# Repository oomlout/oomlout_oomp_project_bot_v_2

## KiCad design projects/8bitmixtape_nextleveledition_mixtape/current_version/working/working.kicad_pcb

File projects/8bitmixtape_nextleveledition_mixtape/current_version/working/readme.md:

# nextleveledition
 
## summary 
* id: 8bitmixtape_nextleveledition_mixtape
* user: 8bitmixtape
* name: nextleveledition
* board: mixtape
* repo: https://github.com/8BitMixtape/NextLevelEdition

* src_file_repo_sch: 
* src_file_repo_sch_link: https://github.com/8BitMixtape/NextLevelEdition/tree/master/
* full details link: https://github.com/oomlout/oomlout_oomp_project_bot_v_2/tree/main/projects/8bitmixtape_nextleveledition_mixtape/current_version/working  

## schematic  
  
[schematic (pdf)](working_schematic.pdf) 

## pcb  

[board (pdf)](working.pdf)  

## working_bom
| Id | Designator | Footprint | Quantity | Designation | Supplier and ref |  | None | 
| --- | --- | --- | --- | --- | --- | --- | --- | 
| 1 | R12,R11 | 0603-RES | 2 | 22 |  |  | [''] | 
| 2 | R6 | 0603-RES | 1 | 10K |  |  | [''] | 
| 3 | LED3 | LED-0603 | 1 | Green |  |  | [''] | 
| 4 | S1 | TASTER-9314_SMD | 1 | Left |  |  | [''] | 
| 5 | BAT+0,BAT-0 | SMD2,54-5,08 | 2 |  |  |  | [''] | 
| 6 | C12,C2,C6,C8,C11,C3 | 0603-CAP | 6 | 1uF |  |  | [''] | 
| 7 | SD0 | MICROSD | 1 | MICROSD |  |  | [''] | 
| 8 | U1 | SOT23-5 | 1 | MCP73831 |  |  | [''] | 
| 9 | U$4 | FUNNEL_LOGO_BOTTOM_V2 | 1 | FIO_LOGOV2 |  |  | [''] | 
| 10 | X1 | USB_B_SMD | 1 | USB_B_SMD |  |  | [''] | 
| 11 | C9 | 0603-CAP | 1 | 4.7uF |  |  | [''] | 
| 12 | C1,C13 | EIA3216 | 2 | 10uF |  |  | [''] | 
| 13 | R16,R13,R4,R10,R3,R7 | 0603-RES | 6 | 330 |  |  | [''] | 
| 14 | R2,R1 | 0603-RES | 2 | 33 |  |  | [''] | 
| 15 | PAD2,PAD3,PAD1 | SMD1,27-2,54 | 3 | WIREPADSMD1,27-254 |  |  | [''] | 
| 16 | Y2 | CRYSTAL-SMD-5X3 | 1 | 8MHz |  |  | [''] | 
| 17 | R9 | 0603-RES | 1 | 470 |  |  | [''] | 
| 18 | LED5,LED1 | LED-0603 | 2 | Yellow |  |  | [''] | 
| 19 | R14,R15 | 0603-RES | 2 | 10k |  |  | [''] | 
| 20 | C7,C5 | 0603-CAP | 2 | 22pF |  |  | [''] | 
| 21 | U$2,U$1 | FIDUCIAL_1MM | 2 | FIDUCIAL |  |  | [''] | 
| 22 | Q1 | SOT23 | 1 | BSS123 |  |  | [''] | 
| 23 | SW0 | SWITCH_SMD | 1 | SWITCH_SMD |  |  | [''] | 
| 24 | POT_RIGHT0,POT_LEFT0 | EVUF | 2 | EVUF2A |  |  | [''] | 
| 25 | U5 | QFN-44-NOPAD_1_1 | 1 | ATMEGA32U4 |  |  | [''] | 
| 26 | LED2 | LED-0603 | 1 | Blue |  |  | [''] | 
| 27 | C14,C4 | 0603-CAP | 2 | 0.1uF |  |  | [''] | 
| 28 | JP4 | 2X3 | 1 | AVR_SPI |  |  | [''] | 
| 29 | R5 | 0603-RES | 1 | 2K |  |  | [''] | 
| 30 | X2 | PJ-327A | 1 | PJ-327A |  |  | [''] | 
| 31 | U6 | SOT23-5 | 1 | MIC5219-3.3 |  |  | [''] | 
| 32 | LED4 | LED-0603 | 1 | Red |  |  | [''] | 
| 33 | SPEAKER0 | PS603 | 1 | PS603SPK |  |  | [''] | 
| 34 | S3 | TASTER-9314_SMD | 1 | Right |  |  | [''] | 
| 35 | LOGO1 | OSHW-LOGO-L | 1 | OSHW-LOGOL |  |  | [''] | 

## bom_schematic
| Ref | Qnty | Value | Cmp name | Footprint | Description | Vendor | DNP | 
| --- | --- | --- | --- | --- | --- | --- | --- | 
| BAT+0 | 1 | SMD5 | SMD5 | working:SMD2,54-5,08 |  |  |  | 
| BAT-0 | 1 | SMD5 | SMD5 | working:SMD2,54-5,08 |  |  |  | 
| C1, C13 | 2 | 10uF | CAP_POL1206 | working:EIA3216 |  |  |  | 
| C2, C3, C6, C8, C11, C12 | 6 | 1uF | CAP0603-CAP | working:0603-CAP |  |  |  | 
| C4, C14 | 2 | 0.1uF | CAP0603-CAP | working:0603-CAP |  |  |  | 
| C5, C7 | 2 | 22pF | CAP0603-CAP | working:0603-CAP |  |  |  | 
| C9 | 1 | 4.7uF | CAP0603-CAP | working:0603-CAP |  |  |  | 
| JP4 | 1 | AVR_SPI_PRG_6PTH | AVR_SPI_PRG_6PTH | working:2X3 |  |  |  | 
| LED1, LED5 | 2 | Yellow | LED0603 | working:LED-0603 |  |  |  | 
| LED2 | 1 | Blue | LED0603 | working:LED-0603 |  |  |  | 
| LED3 | 1 | Green | LED0603 | working:LED-0603 |  |  |  | 
| LED4 | 1 | Red | LED0603 | working:LED-0603 |  |  |  | 
| LOGO1 | 1 | OSHW-LOGOL | OSHW-LOGOL | working:OSHW-LOGO-L |  |  |  | 
| PAD1, PAD2, PAD3 | 3 | WIREPADSMD1,27-254 | WIREPADSMD1,27-254 | working:SMD1,27-2,54 |  |  |  | 
| POT_LEFT0 | 1 | EVUA | EVUA | working:EVUF |  |  |  | 
| POT_RIGHT0 | 1 | EVUA | EVUA | working:EVUF |  |  |  | 
| Q1 | 1 | BSS123 | BSS123 | working:SOT23 |  |  |  | 
| R1, R2 | 2 | 33 | RESISTOR0603-RES | working:0603-RES |  |  |  | 
| R3, R4, R7, R10, R13, R16 | 6 | 330 | RESISTOR0603-RES | working:0603-RES |  |  |  | 
| R5 | 1 | 2K | RESISTOR0603-RES | working:0603-RES |  |  |  | 
| R6 | 1 | 10K | RESISTOR0603-RES | working:0603-RES |  |  |  | 
| R9 | 1 | 470 | RESISTOR0603-RES | working:0603-RES |  |  |  | 
| R11, R12 | 2 | 22 | RESISTOR0603-RES | working:0603-RES |  |  |  | 
| R14, R15 | 2 | 10k | RESISTOR0603-RES | working:0603-RES |  |  |  | 
| S1 | 1 | Left | TASTER-9314_SMD | working:TASTER-9314_SMD |  |  |  | 
| S3 | 1 | Right | TASTER-9314_SMD | working:TASTER-9314_SMD |  |  |  | 
| SD0 | 1 | MICROSD | MICROSD | working:MICROSD |  |  |  | 
| SPEAKER0 | 1 | PS603SPK | PS603SPK | working:PS603 |  |  |  | 
| SW0 | 1 | SWITCH_SMD | SWITCH_SMD | working:SWITCH_SMD |  |  |  | 
| U1 | 1 | MCP73831 | MCP73831 | working:SOT23-5 |  |  |  | 
| U5 | 1 | ATMEGA32U41:1 | ATMEGA32U41{colon}1 | working:QFN-44-NOPAD_1_1 |  |  |  | 
| U6 | 1 | V_REG_LDOSMD | V_REG_LDOSMD | working:SOT23-5 |  |  |  | 
| U$1, U$2 | 2 | FIDUCIAL | FIDUCIAL | working:FIDUCIAL_1MM |  |  |  | 
| X1 | 1 | USB_B_SMD | USB_B_SMD | working:USB_B_SMD |  |  |  | 
| X2 | 1 | PJ-327A | PJ-327A | working:PJ-327A |  |  |  | 
| Y2 | 1 | 8MHz | CRYSTAL5X3 | working:CRYSTAL-SMD-5X3 |  |  |  |

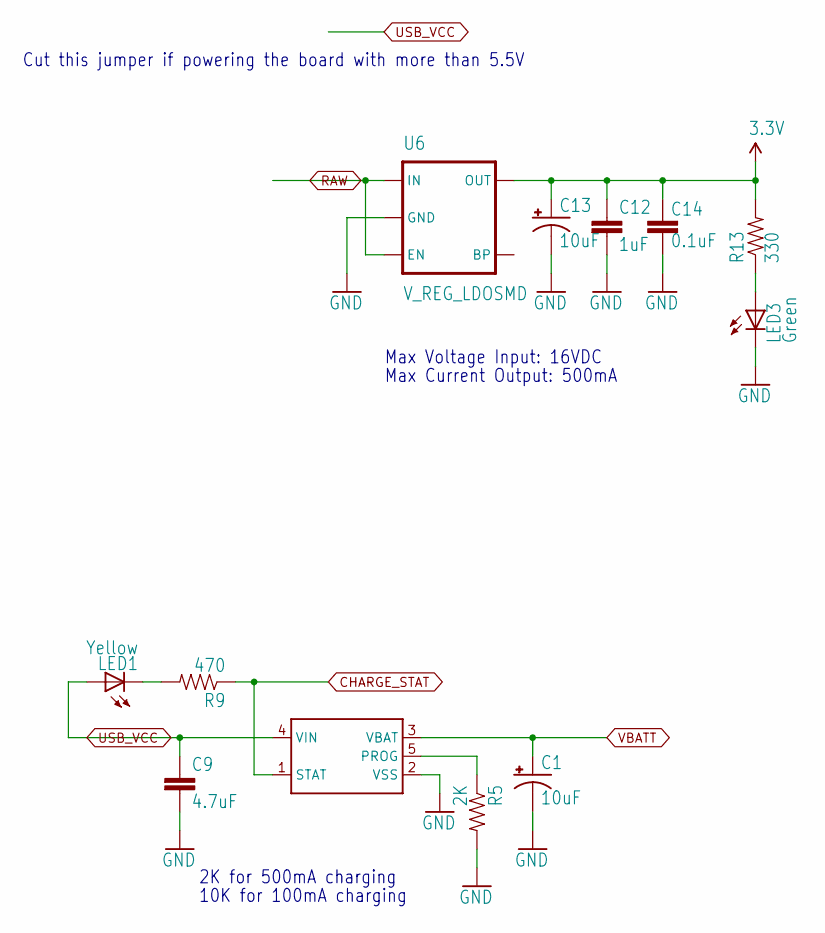
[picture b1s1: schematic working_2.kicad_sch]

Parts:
C1, C13: 10uF; EIA3216
C9: 4.7uF; 0603-CAP
C12: 1uF; 0603-CAP
C14: 0.1uF; 0603-CAP
LED1: Yellow; LED-0603
LED3: Green; LED-0603
R5: 2K; 0603-RES
R9: 470; 0603-RES
R13: 330; 0603-RES
U1: MCP73831; SOT23-5
U6: V_REG_LDOSMD; SOT23-5

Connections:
CHARGE_STAT: R9.1, U1.1 (STAT); also elsewhere on the board
GND: C1.C (-), C9.2, C12.2, C13.C (-), C14.1, LED3.C, R5.2, U1.2 (VSS), U6.2 (GND); also elsewhere on the board
unnamed: LED1.C, R9.2
unnamed: R5.1, U1.5 (PROG)
unnamed: LED3.A, R13.1
RAW: U6.1 (IN), U6.3 (EN); also elsewhere on the board
VBATT: C1.A (+), U1.3 (VBAT); also elsewhere on the board

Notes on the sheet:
Cut this jumper if powering the board with more than 5.5V
10K for 100mA charging
2K for 500mA charging
Max Current Output: 500mA
Max Voltage Input: 16VDC

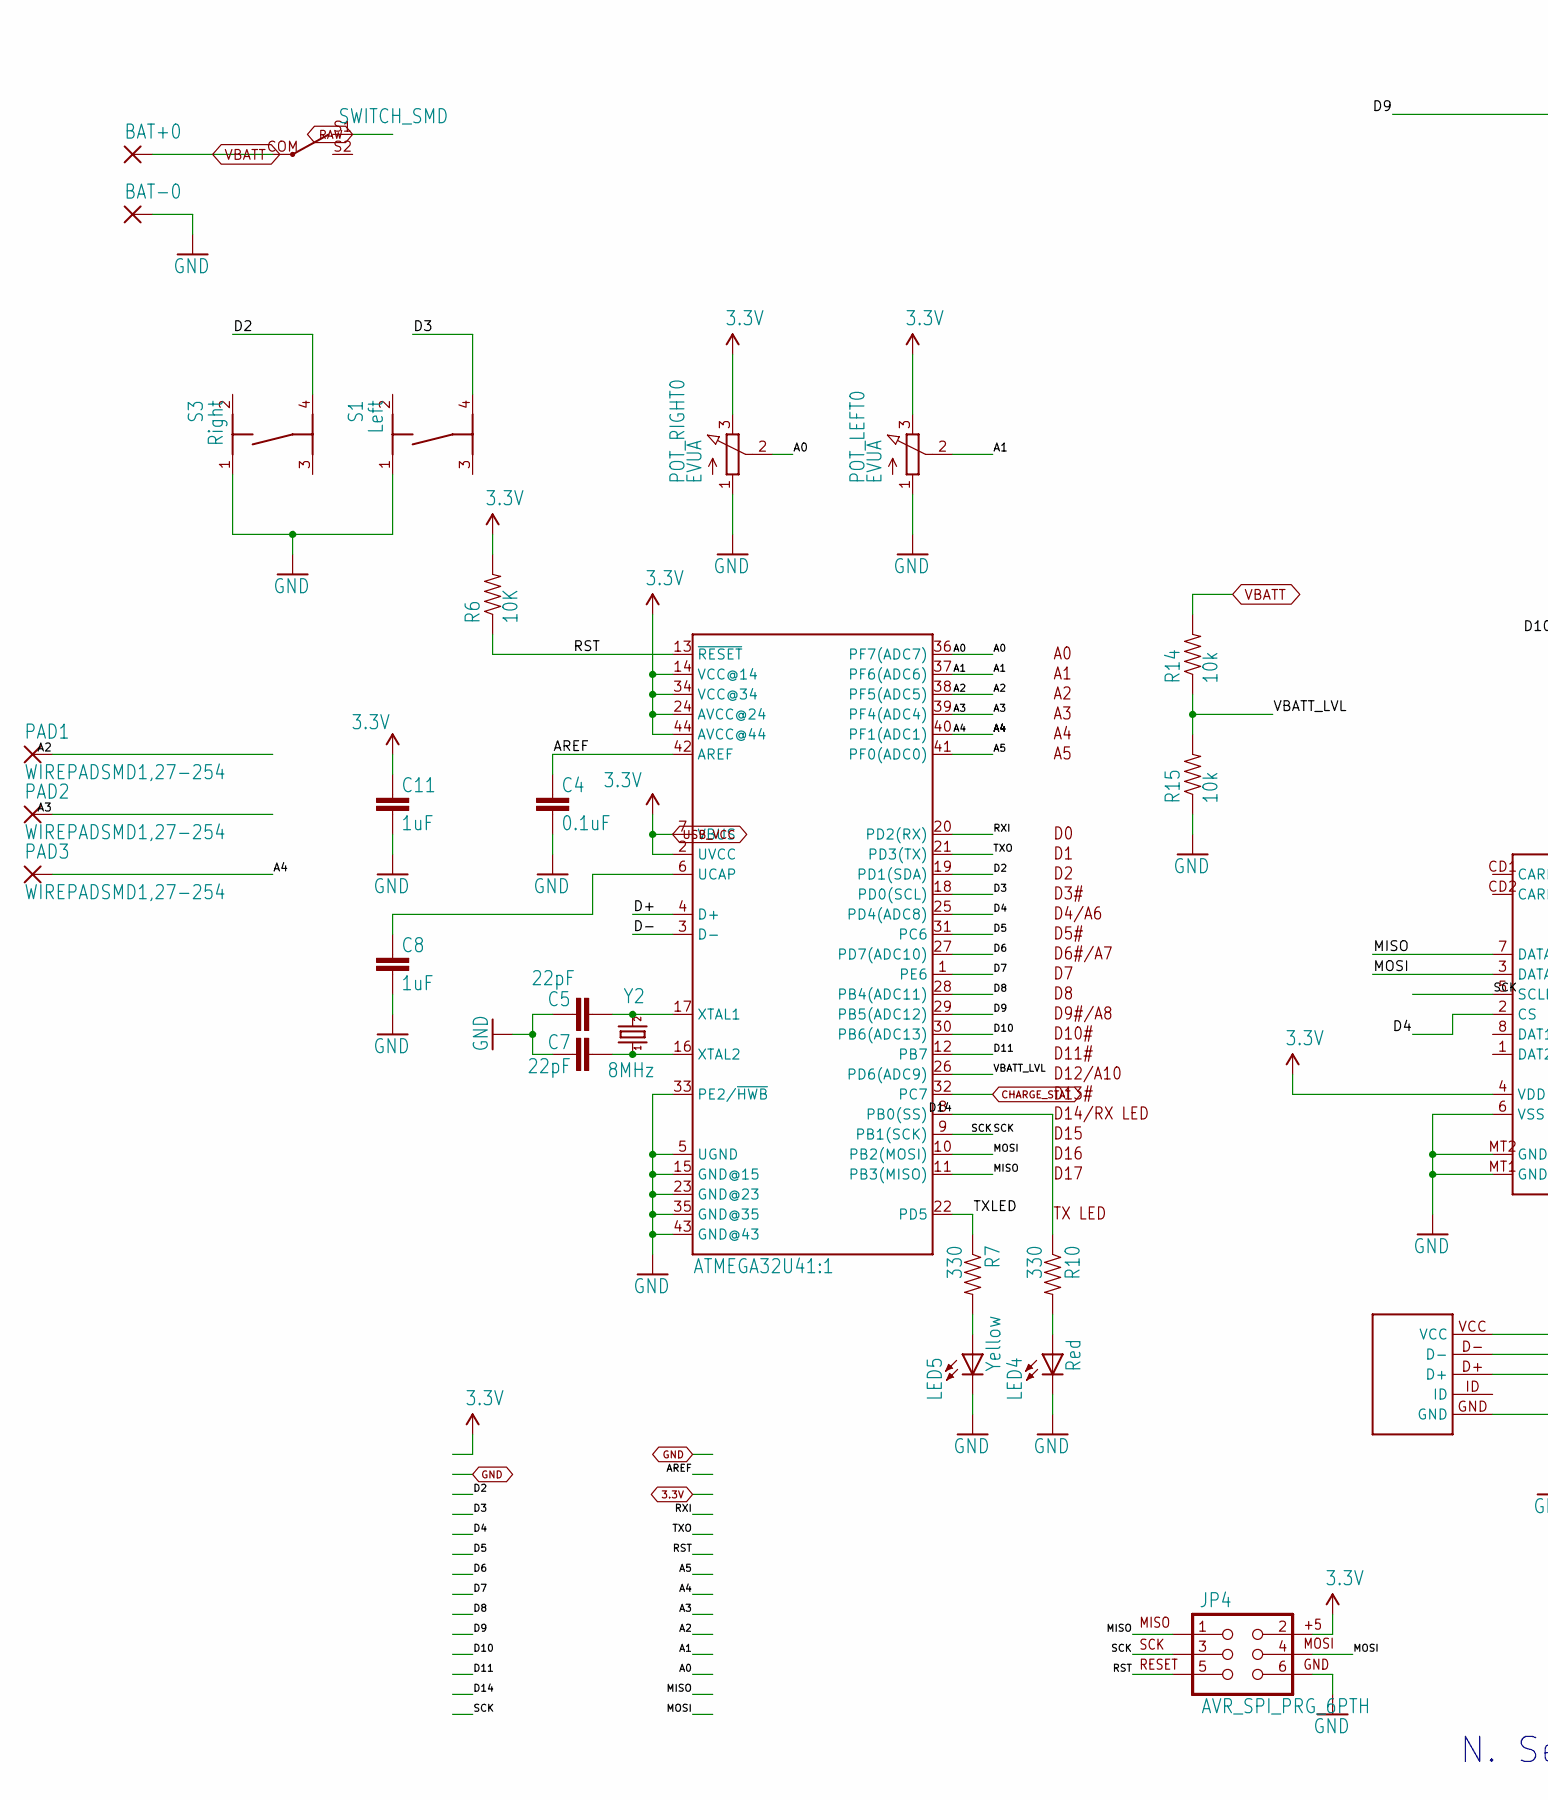
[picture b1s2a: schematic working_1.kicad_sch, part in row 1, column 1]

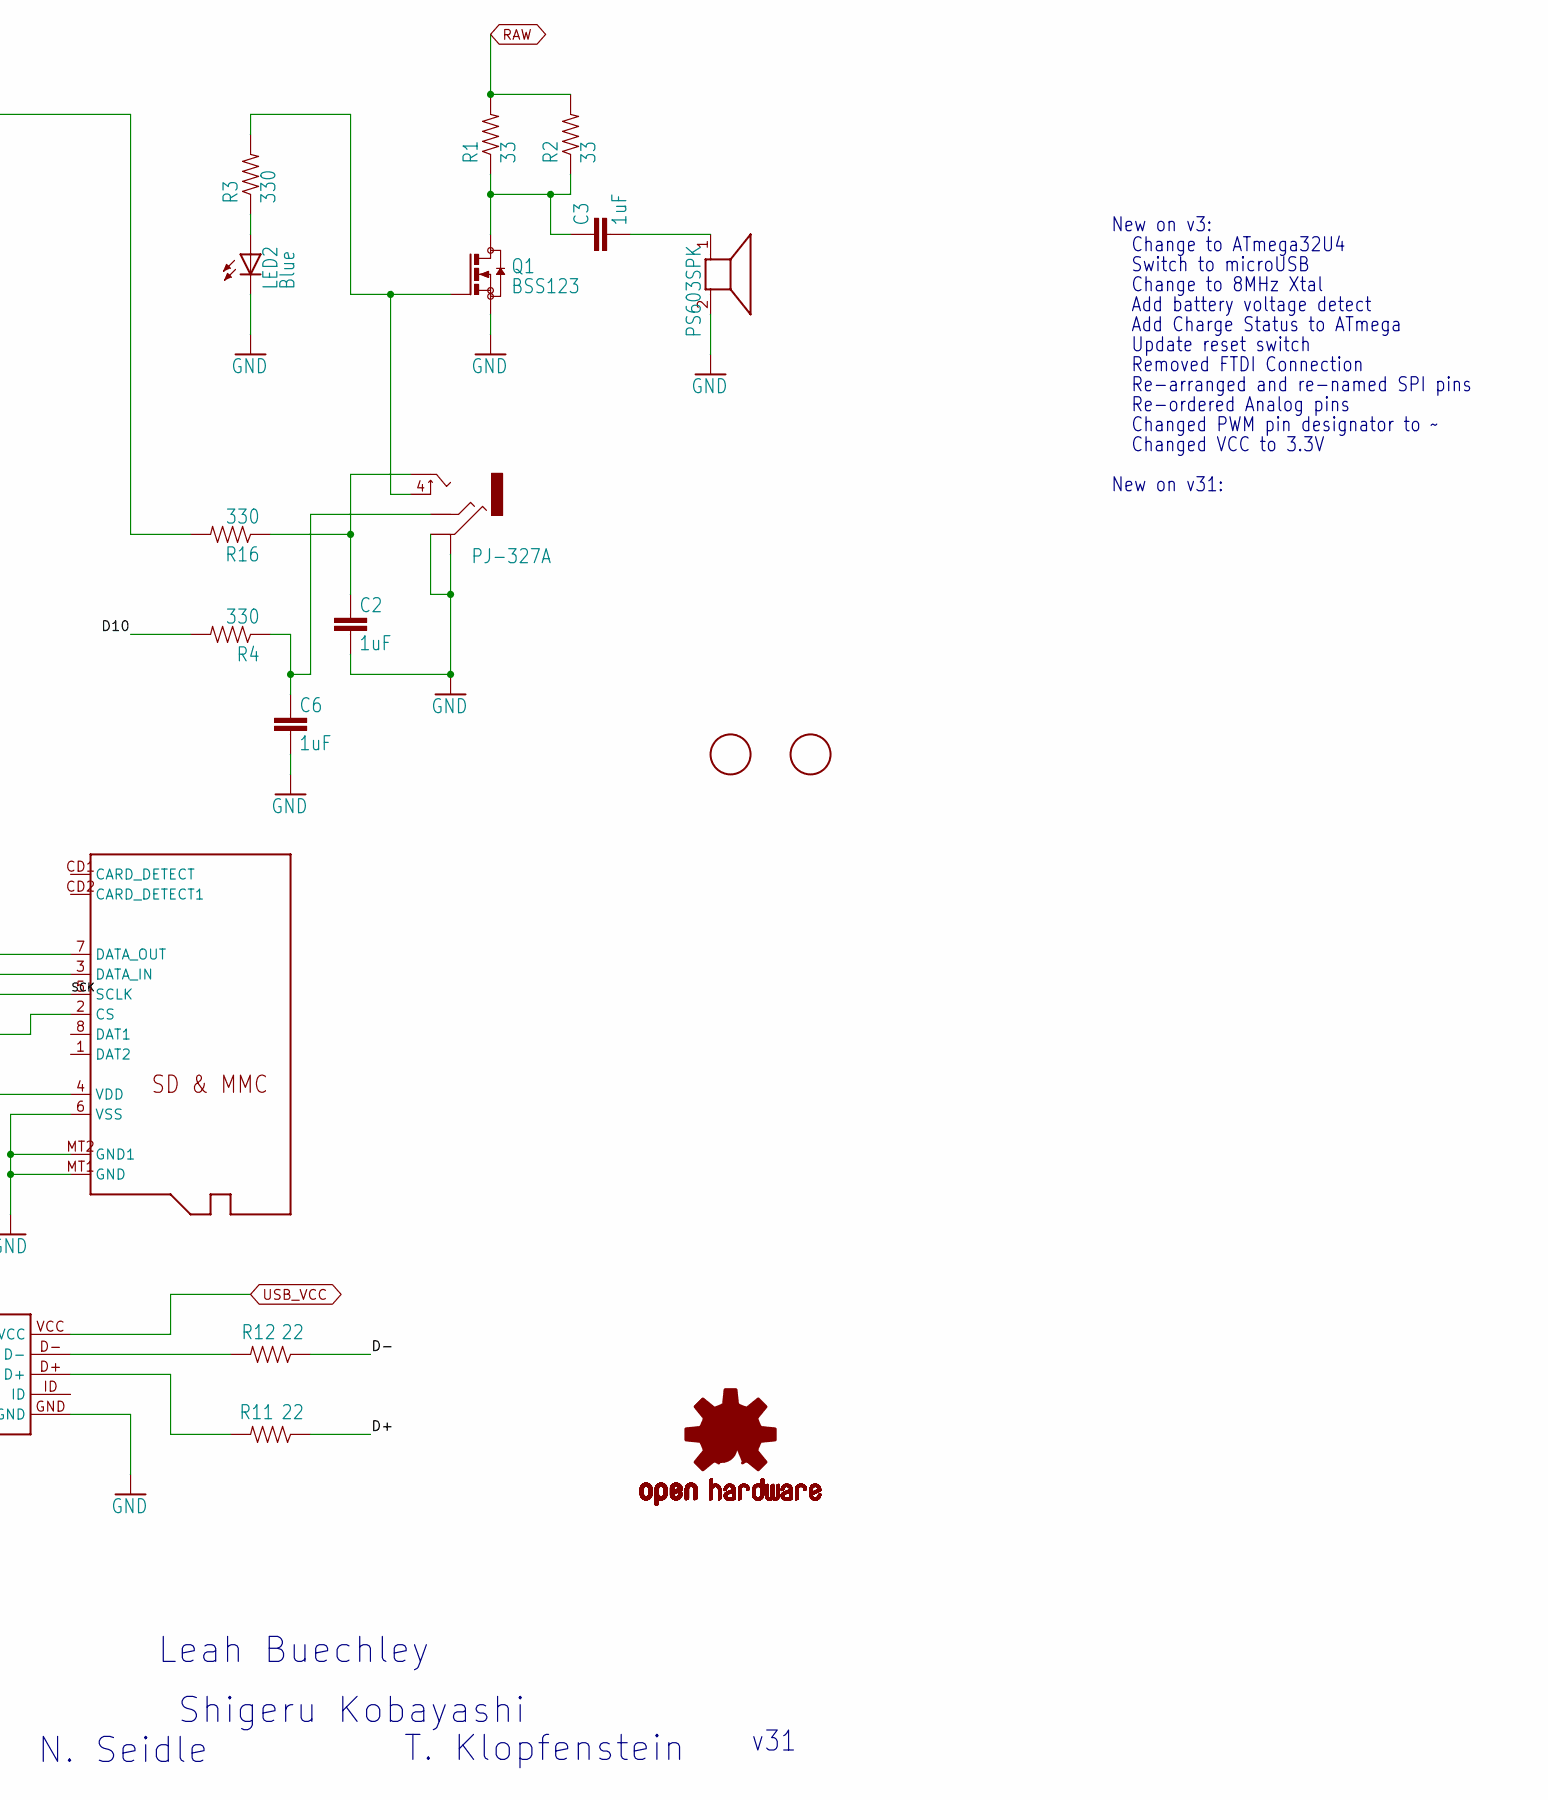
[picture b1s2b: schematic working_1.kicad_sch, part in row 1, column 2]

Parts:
BAT+0: SMD5; SMD2,54-5,08
BAT-0: SMD5; SMD2,54-5,08
C2, C3, C6, C8, C11: 1uF; 0603-CAP
C4: 0.1uF; 0603-CAP
C5, C7: 22pF; 0603-CAP
JP4: AVR_SPI_PRG_6PTH; 2X3
LED2: Blue; LED-0603
LED4: Red; LED-0603
LED5: Yellow; LED-0603
LOGO1: OSHW-LOGOL; OSHW-LOGO-L
PAD1, PAD2, PAD3: WIREPADSMD1,27-254; SMD1,27-2,54
POT_LEFT0: EVUA; EVUF
POT_RIGHT0: EVUA; EVUF
Q1: BSS123; SOT23
R1, R2: 33; 0603-RES
R3, R4, R7, R10, R16: 330; 0603-RES
R6: 10K; 0603-RES
R11, R12: 22; 0603-RES
R14, R15: 10k; 0603-RES
S1: Left; TASTER-9314_SMD
S3: Right; TASTER-9314_SMD
SD0: MICROSD
SPEAKER0: PS603SPK; PS603
SW0: SWITCH_SMD
U5: ATMEGA32U41:1; QFN-44-NOPAD_1_1
U$1, U$2: FIDUCIAL; FIDUCIAL_1MM
X1: USB_B_SMD
X2: PJ-327A
Y2: 8MHz; CRYSTAL-SMD-5X3

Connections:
A0: POT_RIGHT0.2 (S), U5.36 (PF7(ADC7))
A1: POT_LEFT0.2 (S), U5.37 (PF6(ADC6))
A2: PAD1.1, U5.38 (PF5(ADC5))
A3: PAD2.1, U5.39 (PF4(ADC4))
A4: PAD3.1, U5.40 (PF1(ADC1))
A5: U5.41 (PF0(ADC0))
AREF: C4.2, U5.42 (AREF)
CHARGE_STAT: U5.32 (PC7); also elsewhere on the board
D2: S3.4, U5.19 (PD1(SDA))
D3: S1.4, U5.18 (PD0(SCL))
D4: SD0.2 (CS), U5.25 (PD4(ADC8))
D5: U5.31 (PC6)
D6: U5.27 (PD7(ADC10))
D7: U5.1 (PE6)
D8: U5.28 (PB4(ADC11))
D9: R16.2, U5.29 (PB5(ADC12))
D10: R4.2, U5.30 (PB6(ADC13))
D11: U5.12 (PB7)
D14: R10.1, U5.8 (PB0(SS))
D+: R11.1, U5.4 (D+)
D-: R12.1, U5.3 (D-)
GND: BAT-0.1, C2.1, C4.1, C5.2, C6.1, C7.2, C8.1, C11.1, JP4.6, LED2.C, LED4.C, LED5.C, POT_LEFT0.1 (A), POT_RIGHT0.1 (A), Q1.2 (S), R15.1, S1.1, S3.1, SD0.6 (VSS), SD0.MT1 (GND), SD0.MT2 (GND1), SPEAKER0.2, U5.5 (UGND), U5.15 (GND@15), U5.23 (GND@23), U5.33 (PE2/~HWB), U5.35 (GND@35), U5.43 (GND@43), X1.GND, X2.1, X2.5; also elsewhere on the board
MISO: JP4.1, SD0.7 (DATA_OUT), U5.11 (PB3(MISO))
MOSI: JP4.4, SD0.3 (DATA_IN), U5.10 (PB2(MOSI))
unnamed: C3.2, Q1.3 (D), R1.1, R2.1
unnamed: C3.1, SPEAKER0.1
unnamed: C6.2, R4.1, X2.3
unnamed: R11.2, X1.D+
unnamed: LED2.A, R3.1
unnamed: Q1.1 (G), R3.2, X2.4
unnamed: LED5.A, R7.2
unnamed: C7.1, U5.16 (XTAL2), Y2.1
unnamed: C5.1, U5.17 (XTAL1), Y2.3 (2)
unnamed: LED4.A, R10.2
unnamed: R12.2, X1.D-
unnamed: C2.2, R16.1, X2.2
RAW: R1.2, R2.2, SW0.S1; also elsewhere on the board
RST: JP4.5, R6.1, U5.13 (~RESET)
RXI: U5.20 (PD2(RX))
SCK: JP4.3, SD0.5 (SCLK), U5.9 (PB1(SCK))
TXLED: R7.1, U5.22 (PD5)
TXO: U5.21 (PD3(TX))
UCAP: C8.2, U5.6 (UCAP)
VBATT: BAT+0.1, R14.2, SW0.COM; also elsewhere on the board
VBATT_LVL: R14.1, R15.2, U5.26 (PD6(ADC9))

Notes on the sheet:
Switch to microUSB
Update reset switch
Changed PWM pin designator to ~
Re-ordered Analog pins
Re-arranged and re-named SPI pins
N. Seidle
Add Charge Status to ATmega
Change to 8MHz Xtal
New on v3:
Changed VCC to 3.3V
Shigeru Kobayashi
Leah Buechley
Add battery voltage detect
Removed FTDI Connection
Change to ATmega32U4
v31
New on v31:
T. Klopfenstein

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
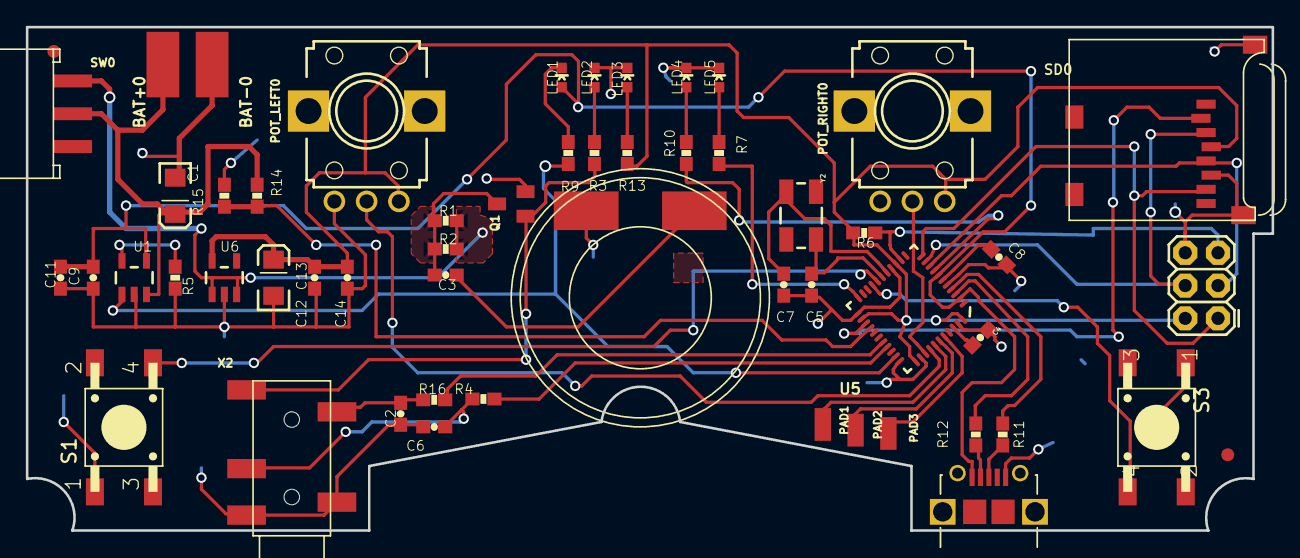
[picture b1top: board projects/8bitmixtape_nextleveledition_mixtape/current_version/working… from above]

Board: 4 copper layers, 96.5 x 39.0 mm, 57 parts (1 on the bottom side), 42 nets.

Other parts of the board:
U$4: FIO_LOGOV2; FUNNEL_LOGO_BOTTOM_V2

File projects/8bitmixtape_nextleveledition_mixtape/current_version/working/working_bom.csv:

"Id";"Designator";"Footprint";"Quantity";"Designation";"Supplier and ref";
1;"R12,R11";"0603-RES";2;"22";;;
2;"R6";"0603-RES";1;"10K";;;
3;"LED3";"LED-0603";1;"Green";;;
4;"S1";"TASTER-9314_SMD";1;"Left";;;
5;"BAT+0,BAT-0";"SMD2,54-5,08";2;"";;;
6;"C12,C2,C6,C8,C11,C3";"0603-CAP";6;"1uF";;;
7;"SD0";"MICROSD";1;"MICROSD";;;
8;"U1";"SOT23-5";1;"MCP73831";;;
9;"U$4";"FUNNEL_LOGO_BOTTOM_V2";1;"FIO_LOGOV2";;;
10;"X1";"USB_B_SMD";1;"USB_B_SMD";;;
11;"C9";"0603-CAP";1;"4.7uF";;;
12;"C1,C13";"EIA3216";2;"10uF";;;
13;"R16,R13,R4,R10,R3,R7";"0603-RES";6;"330";;;
14;"R2,R1";"0603-RES";2;"33";;;
15;"PAD2,PAD3,PAD1";"SMD1,27-2,54";3;"WIREPADSMD1,27-254";;;
16;"Y2";"CRYSTAL-SMD-5X3";1;"8MHz";;;
17;"R9";"0603-RES";1;"470";;;
18;"LED5,LED1";"LED-0603";2;"Yellow";;;
19;"R14,R15";"0603-RES";2;"10k";;;
20;"C7,C5";"0603-CAP";2;"22pF";;;
21;"U$2,U$1";"FIDUCIAL_1MM";2;"FIDUCIAL";;;
22;"Q1";"SOT23";1;"BSS123";;;
23;"SW0";"SWITCH_SMD";1;"SWITCH_SMD";;;
24;"POT_RIGHT0,POT_LEFT0";"EVUF";2;"EVUF2A";;;
25;"U5";"QFN-44-NOPAD_1_1";1;"ATMEGA32U4";;;
26;"LED2";"LED-0603";1;"Blue";;;
27;"C14,C4";"0603-CAP";2;"0.1uF";;;
28;"JP4";"2X3";1;"AVR_SPI";;;
29;"R5";"0603-RES";1;"2K";;;
30;"X2";"PJ-327A";1;"PJ-327A";;;
31;"U6";"SOT23-5";1;"MIC5219-3.3";;;
32;"LED4";"LED-0603";1;"Red";;;
33;"SPEAKER0";"PS603";1;"PS603SPK";;;
34;"S3";"TASTER-9314_SMD";1;"Right";;;
35;"LOGO1";"OSHW-LOGO-L";1;"OSHW-LOGOL";;;

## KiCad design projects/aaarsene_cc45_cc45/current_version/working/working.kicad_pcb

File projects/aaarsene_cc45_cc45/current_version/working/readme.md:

# cc45
 
## summary 
* id: aaarsene_cc45_cc45
* user: aaarsene
* name: cc45
* board: cc45
* repo: https://github.com/aaarsene/CC45
* src_file_repo_kicad_pcb: CC45.kicad_pcb
* src_file_repo_kicad_pcb_link: https://github.com/aaarsene/CC45/tree/master/CC45.kicad_pcb

* src_file_repo_sch: CC45.sch
* src_file_repo_sch_link: https://github.com/aaarsene/CC45/tree/master/CC45.sch
* full details link: https://github.com/oomlout/oomlout_oomp_project_bot_v_2/tree/main/projects/aaarsene_cc45_cc45/current_version/working  

## schematic  
  
[schematic (pdf)](working_schematic.pdf) 

## pcb  

[board (pdf)](working.pdf)  

## working_bom
| Id | Designator | Footprint | Quantity | Designation | Supplier and ref |  | None | 
| --- | --- | --- | --- | --- | --- | --- | --- | 
| 1 | SW2 | MX_19mm-1U-NoLED | 1 | K00 |  |  | [''] | 
| 2 | SW4 | MX_19mm-1U-NoLED | 1 | K02 |  |  | [''] | 
| 3 | SW5 | MX_19mm-1U-NoLED | 1 | K03 |  |  | [''] | 
| 4 | SW6 | MX_19mm-1U-NoLED | 1 | K04 |  |  | [''] | 
| 5 | SW7 | MX_19mm-1U-NoLED | 1 | K05 |  |  | [''] | 
| 6 | SW8 | MX_19mm-1U-NoLED | 1 | K06 |  |  | [''] | 
| 7 | SW9 | MX_19mm-1U-NoLED | 1 | K07 |  |  | [''] | 
| 8 | SW10 | MX_19mm-1U-NoLED | 1 | K08 |  |  | [''] | 
| 9 | SW11 | MX_19mm-1U-NoLED | 1 | K09 |  |  | [''] | 
| 10 | SW12 | MX_19mm-1U-NoLED | 1 | K0A |  |  | [''] | 
| 11 | SW13 | MX_19mm-1U-NoLED | 1 | K0B |  |  | [''] | 
| 12 | SW14 | MX_19mm-1U-NoLED | 1 | K0C |  |  | [''] | 
| 13 | SW16 | MX_19mm-1U-NoLED | 1 | K11 |  |  | [''] | 
| 14 | SW17 | MX_19mm-1U-NoLED | 1 | K12 |  |  | [''] | 
| 15 | SW18 | MX_19mm-1U-NoLED | 1 | K13 |  |  | [''] | 
| 16 | SW19 | MX_19mm-1U-NoLED | 1 | K14 |  |  | [''] | 
| 17 | SW20 | MX_19mm-1U-NoLED | 1 | K15 |  |  | [''] | 
| 18 | SW22 | MX_19mm-1U-NoLED | 1 | K17 |  |  | [''] | 
| 19 | SW23 | MX_19mm-1U-NoLED | 1 | K18 |  |  | [''] | 
| 20 | SW25 | MX_19mm-1U-NoLED | 1 | K1A |  |  | [''] | 
| 21 | SW26 | MX_19mm-1.75U-NoLED | 1 | K1B |  |  | [''] | 
| 22 | SW27 | MX_19mm-1.75U-NoLED | 1 | K20 |  |  | [''] | 
| 23 | SW29 | MX_19mm-1U-NoLED | 1 | K22 |  |  | [''] | 
| 24 | SW30 | MX_19mm-1U-NoLED | 1 | K23 |  |  | [''] | 
| 25 | SW31 | MX_19mm-1U-NoLED | 1 | K24 |  |  | [''] | 
| 26 | SW34 | MX_19mm-1U-NoLED | 1 | K27 |  |  | [''] | 
| 27 | SW35 | MX_19mm-1U-NoLED | 1 | K28 |  |  | [''] | 
| 28 | SW36 | MX_19mm-1U-NoLED | 1 | K29 |  |  | [''] | 
| 29 | SW37 | MX_19mm-1U-NoLED | 1 | K2A |  |  | [''] | 
| 30 | SW38 | MX_19mm-1.25U-NoLED | 1 | K2B |  |  | [''] | 
| 31 | SW24 | MX_19mm-1U-NoLED | 1 | K19 |  |  | [''] | 
| 32 | SW21 | MX_19mm-1U-NoLED | 1 | K16 |  |  | [''] | 
| 33 | SW33 | MX_19mm-1U-NoLED | 1 | K26 |  |  | [''] | 
| 34 | SW32 | MX_19mm-1U-NoLED | 1 | K25 |  |  | [''] | 
| 35 | SW39 | MX_19mm-1U-NoLED | 1 | K30 |  |  | [''] | 
| 36 | SW40,SW40 | MX_19mm-1U-NoLED | 2 | K31 |  |  | [''] | 
| 37 | SW42 | MX_19mm-1U-NoLED | 1 | K33 |  |  | [''] | 
| 38 | SW45 | MX_19mm-1U-NoLED | 1 | K38 |  |  | [''] | 
| 39 | SW41 | MX_19mm-1U-NoLED | 1 | K32 |  |  | [''] | 
| 40 | SW43 | MX_19mm-2.25U-ReversedStabilizers-NoLED | 1 | K34 |  |  | [''] | 
| 41 | SW46 | MX_19mm-1U-NoLED | 1 | K39 |  |  | [''] | 
| 42 | SW48 | MX_19mm-1U-NoLED | 1 | K3B |  |  | [''] | 
| 43 | SW44 | MX_19mm-2.75U-ReversedStabilizers-NoLED | 1 | K36 |  |  | [''] | 
| 44 | SW47,SW47 | MX_19mm-1U-NoLED | 2 | K3A |  |  | [''] | 
| 45 | SW15 | MX_19mm-1.25U-NoLED | 1 | K10 |  |  | [''] | 
| 46 | G*** | cc | 1 | LOGO |  |  | [''] | 
| 47 | SW3 | MX_19mm-1U-NoLED | 1 | K01 |  |  | [''] | 
| 48 | SW39 | MX_19mm-1.5U-NoLED | 1 | K30 |  |  | [''] | 
| 49 | SW42 | MX_19mm-1.5U-NoLED | 1 | K33 |  |  | [''] | 
| 50 | SW45 | MX_19mm-1.5U-NoLED | 1 | K38 |  |  | [''] | 
| 51 | SW48 | MX_19mm-1.5U-NoLED | 1 | K3B |  |  | [''] | 
| 52 | SW40 | MX_19mm-1.5U-NoLED | 1 | K31 |  |  | [''] | 
| 53 | SW47 | MX_19mm-1.5U-NoLED | 1 | K3A |  |  | [''] | 
| 54 | SW43 | MX_19mm-7U-ReversedStabilizers-NoLED | 1 | K34 |  |  | [''] | 
| 55 | SW28 | MX_19mm-1U-NoLED | 1 | K21 |  |  | [''] | 
| 56 | C1 | C_1206_3216Metric_Pad1.42x1.75mm_HandSolder | 1 | 1u |  |  | [''] | 
| 57 | D1,D2,D3,D4,D5,D6,D7,D8,D9,D10,D11,D12,D14,D16,D17,D18,D20,D21,D22,D23,D24,D25,D26,D27,D28,D29,D30,D31,D32,D33,D34,D35,D36,D37,D38,D39,D40,D41,D42,D43,D44,D46,D47,D19,D13,D15,D45 | D_SOD-323_HandSoldering | 47 | D |  |  | [''] | 
| 58 | R4,R1 | R_1206_3216Metric_Pad1.42x1.75mm_HandSolder | 2 | 10k |  |  | [''] | 
| 59 | USB1 | HRO-TYPE-C-31-M-12-HandSoldering | 1 | HRO-TYPE-C-31-M-12 |  |  | [''] | 
| 60 | SW1 | SKQG-1155865 | 1 | RESET |  |  | [''] | 
| 61 | R3,R2 | R_1206_3216Metric_Pad1.42x1.75mm_HandSolder | 2 | 22 |  |  | [''] | 
| 62 | C7,C6 | C_1206_3216Metric_Pad1.42x1.75mm_HandSolder | 2 | 22p |  |  | [''] | 
| 63 | X1 | Crystal_SMD_3225-4Pin_3.2x2.5mm_HandSoldering | 1 | XTAL |  |  | [''] | 
| 64 | C4,C8,C3,C2 | C_1206_3216Metric_Pad1.42x1.75mm_HandSolder | 4 | 0.1u |  |  | [''] | 
| 65 | F1 | Fuse_1206_3216Metric_Pad1.42x1.75mm_HandSolder | 1 | 500m |  |  | [''] | 
| 66 | R5,R6 | R_1206_3216Metric_Pad1.42x1.75mm_HandSolder | 2 | 5.1k |  |  | [''] | 
| 67 | U2 | SOT143B | 1 | PRTR5V0U2X |  |  | [''] | 
| 68 | U1 | TQFP-44_10x10mm_P0.8mm | 1 | ATmega32U4-AU |  |  | [''] | 
| 69 | C5 | C_1206_3216Metric_Pad1.42x1.75mm_HandSolder | 1 | 10u |  |  | [''] | 

## bom_schematic
| Ref | Qnty | Value | Cmp name | Footprint | Description | Vendor | DNP | 
| --- | --- | --- | --- | --- | --- | --- | --- | 
| C1 | 1 | 1u | C_Small | Capacitor_SMD:C_1206_3216Metric_Pad1.42x1.75mm_HandSolder | Unpolarized capacitor, small symbol |  |  | 
| C2, C3, C4, C8 | 4 | 0.1u | C_Small | Capacitor_SMD:C_1206_3216Metric_Pad1.42x1.75mm_HandSolder | Unpolarized capacitor, small symbol |  |  | 
| C5 | 1 | 10u | C_Small | Capacitor_SMD:C_1206_3216Metric_Pad1.42x1.75mm_HandSolder | Unpolarized capacitor, small symbol |  |  | 
| C6, C7 | 2 | 22p | C_Small | Capacitor_SMD:C_1206_3216Metric_Pad1.42x1.75mm_HandSolder | Unpolarized capacitor, small symbol |  |  | 
| F1 | 1 | 500m | Polyfuse_Small | Fuse:Fuse_1206_3216Metric_Pad1.42x1.75mm_HandSolder | Resettable fuse, polymeric positive temperature coefficient, small symbol |  |  | 
| J1 | 1 | AVR-ISP-6 | AVR-ISP-6 | random-keyboard-parts:Reset_Pretty-Mask | Atmel 6-pin ISP connector |  |  | 
| R1, R4 | 2 | 10k | R_Small | Resistor_SMD:R_1206_3216Metric_Pad1.42x1.75mm_HandSolder | Resistor, small symbol |  |  | 
| R2, R3 | 2 | 22 | R_Small | Resistor_SMD:R_1206_3216Metric_Pad1.42x1.75mm_HandSolder | Resistor, small symbol |  |  | 
| R5, R6 | 2 | 5.1k | R_Small | Resistor_SMD:R_1206_3216Metric_Pad1.42x1.75mm_HandSolder | Resistor, small symbol |  |  | 
| SW1 | 1 | RESET | SW_Push_Dual | random-keyboard-parts:SKQG-1155865 | Push button switch, generic, symbol, four pins |  |  | 
| U1 | 1 | ATmega32U4-AU | ATmega32U4-AU-MCU_Microchip_ATmega | Package_QFP:TQFP-44_10x10mm_P0.8mm |  |  |  | 
| U2 | 1 | PRTR5V0U2X | PRTR5V0U2X-random-keyboard-parts | random-keyboard-parts:SOT143B |  |  |  | 
| USB1 | 1 | HRO-TYPE-C-31-M-12 | HRO-TYPE-C-31-M-12-Type-C | Type-C:HRO-TYPE-C-31-M-12-HandSoldering |  |  |  | 
| X1 | 1 | XTAL | Crystal_GND24_Small | Crystal:Crystal_SMD_3225-4Pin_3.2x2.5mm_HandSoldering | Four pin crystal, GND on pins 2 and 4, small symbol |  |  |

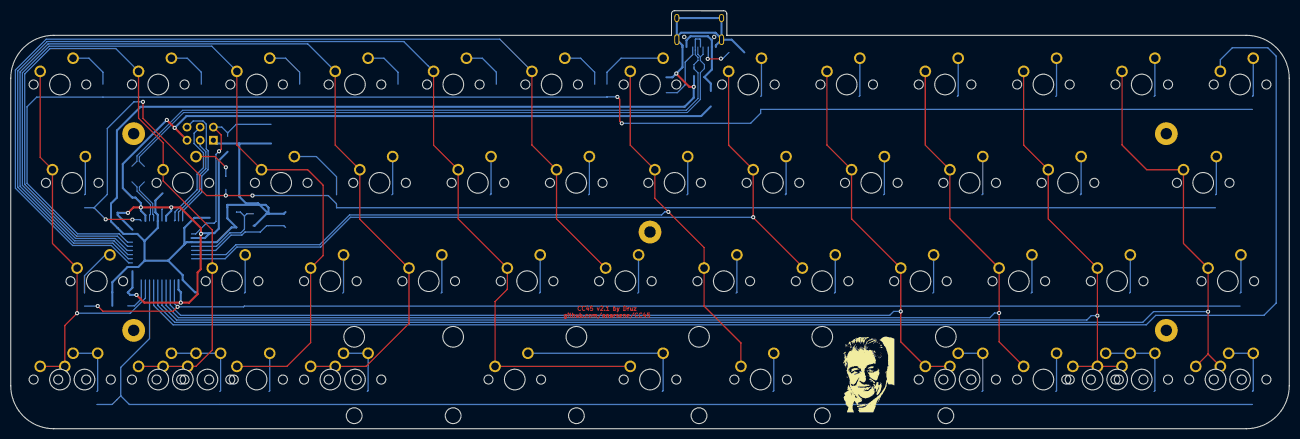
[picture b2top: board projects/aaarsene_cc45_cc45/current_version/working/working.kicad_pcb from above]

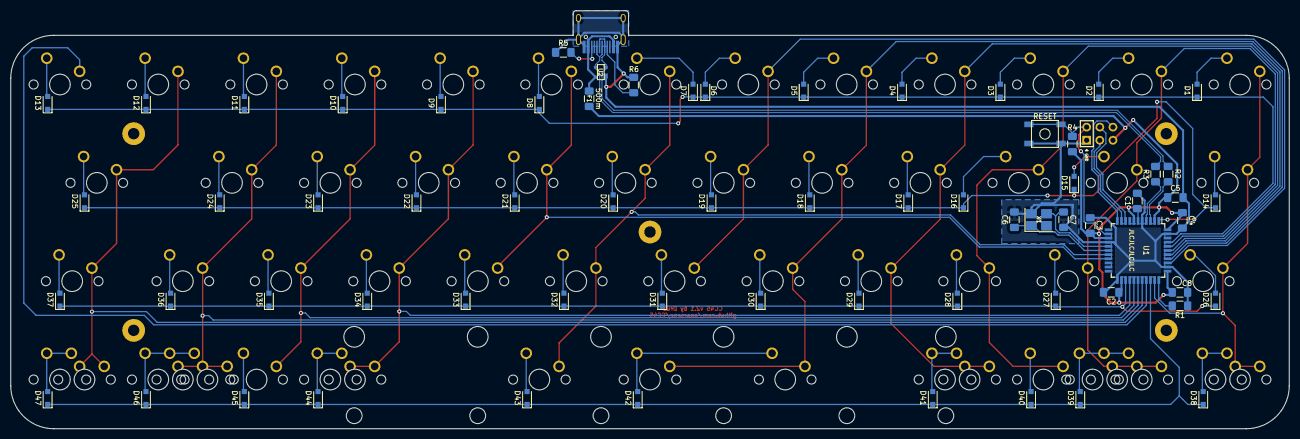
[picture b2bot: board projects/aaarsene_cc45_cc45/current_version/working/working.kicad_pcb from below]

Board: 2 copper layers, 247.0 x 80.8 mm, 124 parts (68 on the bottom side), 81 nets.

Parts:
C1: 1u; C_1206_3216Metric_Pad1.42x1.75mm_HandSolder
C2, C3, C4, C8: 0.1u; C_1206_3216Metric_Pad1.42x1.75mm_HandSolder
C5: 10u; C_1206_3216Metric_Pad1.42x1.75mm_HandSolder
C6, C7: 22p; C_1206_3216Metric_Pad1.42x1.75mm_HandSolder
D1, D2, D3, D4, D5, D6, D7, D8, D9, D10, D11, D12, D13, D14, D15, D16, D17, D18, D19, D20, D21, D22, D23, D24, D25, D26, D27, D28, D29, D30, D31, D32, D33, D34, D35, D36, D37, D38, D39, D40, D41, D42, D43, D44, D45, D46, D47: D; D_SOD-323_HandSoldering
F1: 500m; Fuse_1206_3216Metric_Pad1.42x1.75mm_HandSolder
J1: AVR-ISP-6; Reset_Pretty-Mask
R1, R4: 10k; R_1206_3216Metric_Pad1.42x1.75mm_HandSolder
R2, R3: 22; R_1206_3216Metric_Pad1.42x1.75mm_HandSolder
R5, R6: 5.1k; R_1206_3216Metric_Pad1.42x1.75mm_HandSolder
SW1: RESET; SKQG-1155865
SW2: K00; MX_19mm-1U-NoLED
SW3: K01; MX_19mm-1U-NoLED
SW4: K02; MX_19mm-1U-NoLED
SW5: K03; MX_19mm-1U-NoLED
SW6: K04; MX_19mm-1U-NoLED
SW7: K05; MX_19mm-1U-NoLED
SW8: K06; MX_19mm-1U-NoLED
SW9: K07; MX_19mm-1U-NoLED
SW10: K08; MX_19mm-1U-NoLED
SW11: K09; MX_19mm-1U-NoLED
SW12: K0A; MX_19mm-1U-NoLED
SW13: K0B; MX_19mm-1U-NoLED
SW14: K0C; MX_19mm-1U-NoLED
SW15: K10; MX_19mm-1.25U-NoLED
SW16: K11; MX_19mm-1U-NoLED
SW17: K12; MX_19mm-1U-NoLED
SW18: K13; MX_19mm-1U-NoLED
SW19: K14; MX_19mm-1U-NoLED
SW20: K15; MX_19mm-1U-NoLED
SW21: K16; MX_19mm-1U-NoLED
SW22: K17; MX_19mm-1U-NoLED
SW23: K18; MX_19mm-1U-NoLED
SW24: K19; MX_19mm-1U-NoLED
SW25: K1A; MX_19mm-1U-NoLED
SW26: K1B; MX_19mm-1.75U-NoLED
SW27: K20; MX_19mm-1.75U-NoLED
SW28: K21; MX_19mm-1U-NoLED
SW29: K22; MX_19mm-1U-NoLED
SW30: K23; MX_19mm-1U-NoLED
SW31: K24; MX_19mm-1U-NoLED
SW32: K25; MX_19mm-1U-NoLED
SW33: K26; MX_19mm-1U-NoLED
SW34: K27; MX_19mm-1U-NoLED
SW35: K28; MX_19mm-1U-NoLED
SW36: K29; MX_19mm-1U-NoLED
SW37: K2A; MX_19mm-1U-NoLED
SW38: K2B; MX_19mm-1.25U-NoLED
SW39: K30; MX_19mm-1U-NoLED
SW39#2: K30; MX_19mm-1.5U-NoLED
SW40, SW40#2: K31; MX_19mm-1U-NoLED
SW40#3: K31; MX_19mm-1.5U-NoLED
SW41: K32; MX_19mm-1U-NoLED
SW42: K33; MX_19mm-1U-NoLED
SW42#2: K33; MX_19mm-1.5U-NoLED
SW43: K34; MX_19mm-2.25U-ReversedStabilizers-NoLED
SW43#2: K34; MX_19mm-7U-ReversedStabilizers-NoLED
SW44: K36; MX_19mm-2.75U-ReversedStabilizers-NoLED
SW45: K38; MX_19mm-1U-NoLED
SW45#2: K38; MX_19mm-1.5U-NoLED
SW46: K39; MX_19mm-1U-NoLED
SW47, SW47#2: K3A; MX_19mm-1U-NoLED
SW47#3: K3A; MX_19mm-1.5U-NoLED
SW48: K3B; MX_19mm-1U-NoLED
SW48#2: K3B; MX_19mm-1.5U-NoLED
U1: ATmega32U4-AU; TQFP-44_10x10mm_P0.8mm
U2: PRTR5V0U2X; SOT143B
USB1: HRO-TYPE-C-31-M-12; HRO-TYPE-C-31-M-12-HandSoldering
X1: XTAL; Crystal_SMD_3225-4Pin_3.2x2.5mm_HandSoldering

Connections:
+5V: C2.1, C3.1, C4.1, C5.1, C8.1, F1.1, J1.2, R4.2, U1.2, U1.7, U1.14, U1.24, U1.34, U1.44
/USB_N: R2.2, U2.2, USB1.5, USB1.7
/USB_P: R3.2, U2.3, USB1.6, USB1.8
D+: R3.1, U1.4
D-: R2.1, U1.3
GND: C1.2, C2.2, C3.2, C4.2, C5.2, C6.2, C7.2, C8.2, J1.6, R1.1, R5.1, R6.1, SW1.1, SW1.3, U1.5, U1.15, U1.23, U1.35, U1.43, U2.1, USB1.1, USB1.12, USB1.13, X1.2, X1.4
MISO: J1.1, U1.11
MOSI: J1.4, U1.10
unnamed: C1.1, U1.6
unnamed: D1.2, SW2.1
unnamed: D2.2, SW3.1
unnamed: D3.2, SW4.1
unnamed: D4.2, SW5.1
unnamed: D5.2, SW6.1
unnamed: D6.2, SW7.1
unnamed: D7.2, SW8.1
unnamed: D8.2, SW9.1
unnamed: D9.2, SW10.1
unnamed: D10.2, SW11.1
unnamed: D11.2, SW12.1
unnamed: D12.2, SW13.1
unnamed: D13.2, SW14.1
unnamed: D14.2, SW15.1
unnamed: D15.2, SW16.1
unnamed: D16.2, SW17.1
unnamed: D17.2, SW18.1
unnamed: D18.2, SW19.1
unnamed: D19.2, SW20.1
unnamed: D20.2, SW21.1
unnamed: D21.2, SW22.1
unnamed: D22.2, SW23.1
unnamed: D23.2, SW24.1
unnamed: D24.2, SW25.1
unnamed: D25.2, SW26.1
unnamed: D26.2, SW27.1
unnamed: D27.2, SW28.1
unnamed: D28.2, SW29.1
unnamed: D29.2, SW30.1
unnamed: D30.2, SW31.1
unnamed: D31.2, SW32.1
unnamed: D32.2, SW33.1
unnamed: D33.2, SW34.1
unnamed: D34.2, SW35.1
unnamed: D35.2, SW36.1
unnamed: D36.2, SW37.1
unnamed: D37.2, SW38.1
unnamed: D38.2, SW39.1, SW39#2.1
unnamed: D39.2, SW40.1, SW40#2.1, SW40#3.1
unnamed: D40.2, SW41.1
unnamed: D41.2, SW42.1, SW42#2.1
unnamed: D42.2, SW43.1, SW43#2.1
unnamed: D43.2, SW44.1
unnamed: D44.2, SW45.1, SW45#2.1
unnamed: D45.2, SW46.1
unnamed: D46.2, SW47.1, SW47#2.1, SW47#3.1
unnamed: D47.2, SW48.1, SW48#2.1
unnamed: R1.2, U1.33
unnamed: R5.2, USB1.10
unnamed: R6.2, USB1.4
RESET: J1.5, R4.1, SW1.2, SW1.4, U1.13
SCK: J1.3, U1.9
VCC: F1.2, U2.4, USB1.2, USB1.11
XTAL1: C6.1, U1.17, X1.1
XTAL2: C7.1, U1.16, X1.3
col0: SW2.2, SW15.2, SW27.2, SW39.2, SW39#2.2, U1.32
col1: SW3.2, SW16.2, SW28.2, SW40.2, SW40#2.2, SW40#3.2, U1.40
col2: SW4.2, SW17.2, SW29.2, SW41.2, U1.39
col3: SW5.2, SW18.2, SW30.2, SW42.2, SW42#2.2, U1.38
col4: SW6.2, SW19.2, SW31.2, SW43.2, SW43#2.2, U1.37
col5: SW7.2, SW20.2, SW32.2, U1.36
col6: SW8.2, SW21.2, SW33.2, SW44.2, U1.18
col7: SW9.2, SW22.2, SW34.2, U1.19
col8: SW10.2, SW23.2, SW35.2, SW45.2, SW45#2.2, U1.26
col9: SW11.2, SW24.2, SW36.2, SW46.2, U1.27
col10: SW12.2, SW25.2, SW37.2, SW47.2, SW47#2.2, SW47#3.2, U1.28
col11: SW13.2, SW26.2, SW38.2, SW48.2, SW48#2.2, U1.29
col12: SW14.2, U1.30
row0: D1.1, D2.1, D3.1, D4.1, D5.1, D6.1, D7.1, D8.1, D9.1, D10.1, D11.1, D12.1, D13.1, U1.41
row1: D14.1, D15.1, D16.1, D17.1, D18.1, D19.1, D20.1, D21.1, D22.1, D23.1, D24.1, D25.1, U1.1
row2: D26.1, D27.1, D28.1, D29.1, D30.1, D31.1, D32.1, D33.1, D34.1, D35.1, D36.1, D37.1, U1.25
row3: D38.1, D39.1, D40.1, D41.1, D42.1, D43.1, D44.1, D45.1, D46.1, D47.1, U1.31

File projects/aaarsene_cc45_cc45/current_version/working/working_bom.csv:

"Id";"Designator";"Footprint";"Quantity";"Designation";"Supplier and ref";
1;"SW2";"MX_19mm-1U-NoLED";1;"K00";;;
2;"SW4";"MX_19mm-1U-NoLED";1;"K02";;;
3;"SW5";"MX_19mm-1U-NoLED";1;"K03";;;
4;"SW6";"MX_19mm-1U-NoLED";1;"K04";;;
5;"SW7";"MX_19mm-1U-NoLED";1;"K05";;;
6;"SW8";"MX_19mm-1U-NoLED";1;"K06";;;
7;"SW9";"MX_19mm-1U-NoLED";1;"K07";;;
8;"SW10";"MX_19mm-1U-NoLED";1;"K08";;;
9;"SW11";"MX_19mm-1U-NoLED";1;"K09";;;
10;"SW12";"MX_19mm-1U-NoLED";1;"K0A";;;
11;"SW13";"MX_19mm-1U-NoLED";1;"K0B";;;
12;"SW14";"MX_19mm-1U-NoLED";1;"K0C";;;
13;"SW16";"MX_19mm-1U-NoLED";1;"K11";;;
14;"SW17";"MX_19mm-1U-NoLED";1;"K12";;;
15;"SW18";"MX_19mm-1U-NoLED";1;"K13";;;
16;"SW19";"MX_19mm-1U-NoLED";1;"K14";;;
17;"SW20";"MX_19mm-1U-NoLED";1;"K15";;;
18;"SW22";"MX_19mm-1U-NoLED";1;"K17";;;
19;"SW23";"MX_19mm-1U-NoLED";1;"K18";;;
20;"SW25";"MX_19mm-1U-NoLED";1;"K1A";;;
21;"SW26";"MX_19mm-1.75U-NoLED";1;"K1B";;;
22;"SW27";"MX_19mm-1.75U-NoLED";1;"K20";;;
23;"SW29";"MX_19mm-1U-NoLED";1;"K22";;;
24;"SW30";"MX_19mm-1U-NoLED";1;"K23";;;
25;"SW31";"MX_19mm-1U-NoLED";1;"K24";;;
26;"SW34";"MX_19mm-1U-NoLED";1;"K27";;;
27;"SW35";"MX_19mm-1U-NoLED";1;"K28";;;
28;"SW36";"MX_19mm-1U-NoLED";1;"K29";;;
29;"SW37";"MX_19mm-1U-NoLED";1;"K2A";;;
30;"SW38";"MX_19mm-1.25U-NoLED";1;"K2B";;;
31;"SW24";"MX_19mm-1U-NoLED";1;"K19";;;
32;"SW21";"MX_19mm-1U-NoLED";1;"K16";;;
33;"SW33";"MX_19mm-1U-NoLED";1;"K26";;;
34;"SW32";"MX_19mm-1U-NoLED";1;"K25";;;
35;"SW39";"MX_19mm-1U-NoLED";1;"K30";;;
36;"SW40,SW40";"MX_19mm-1U-NoLED";2;"K31";;;
37;"SW42";"MX_19mm-1U-NoLED";1;"K33";;;
38;"SW45";"MX_19mm-1U-NoLED";1;"K38";;;
39;"SW41";"MX_19mm-1U-NoLED";1;"K32";;;
40;"SW43";"MX_19mm-2.25U-ReversedStabilizers-NoLED";1;"K34";;;
41;"SW46";"MX_19mm-1U-NoLED";1;"K39";;;
42;"SW48";"MX_19mm-1U-NoLED";1;"K3B";;;
43;"SW44";"MX_19mm-2.75U-ReversedStabilizers-NoLED";1;"K36";;;
44;"SW47,SW47";"MX_19mm-1U-NoLED";2;"K3A";;;
45;"SW15";"MX_19mm-1.25U-NoLED";1;"K10";;;
46;"G***";"cc";1;"LOGO";;;
47;"SW3";"MX_19mm-1U-NoLED";1;"K01";;;
48;"SW39";"MX_19mm-1.5U-NoLED";1;"K30";;;
49;"SW42";"MX_19mm-1.5U-NoLED";1;"K33";;;
50;"SW45";"MX_19mm-1.5U-NoLED";1;"K38";;;
51;"SW48";"MX_19mm-1.5U-NoLED";1;"K3B";;;
52;"SW40";"MX_19mm-1.5U-NoLED";1;"K31";;;
53;"SW47";"MX_19mm-1.5U-NoLED";1;"K3A";;;
54;"SW43";"MX_19mm-7U-ReversedStabilizers-NoLED";1;"K34";;;
55;"SW28";"MX_19mm-1U-NoLED";1;"K21";;;
56;"C1";"C_1206_3216Metric_Pad1.42x1.75mm_HandSolder";1;"1u";;;
57;"D1,D2,D3,D4,D5,D6,D7,D8,D9,D10,D11,D12,D14,D16,D17,D18,D20,D21,D22,D23,D24,D25,D26,D27,D28,D29,D30,D31,D32,D33,D34,D35,D36,D37,D38,D39,D40,D41,D42,D43,D44,D46,D47,D19,D13,D15,D45";"D_SOD-323_HandSoldering";47;"D";;;
58;"R4,R1";"R_1206_3216Metric_Pad1.42x1.75mm_HandSolder";2;"10k";;;
59;"USB1";"HRO-TYPE-C-31-M-12-HandSoldering";1;"HRO-TYPE-C-31-M-12";;;
60;"SW1";"SKQG-1155865";1;"RESET";;;
61;"R3,R2";"R_1206_3216Metric_Pad1.42x1.75mm_HandSolder";2;"22";;;
62;"C7,C6";"C_1206_3216Metric_Pad1.42x1.75mm_HandSolder";2;"22p";;;
63;"X1";"Crystal_SMD_3225-4Pin_3.2x2.5mm_HandSoldering";1;"XTAL";;;
64;"C4,C8,C3,C2";"C_1206_3216Metric_Pad1.42x1.75mm_HandSolder";4;"0.1u";;;
65;"F1";"Fuse_1206_3216Metric_Pad1.42x1.75mm_HandSolder";1;"500m";;;
66;"R5,R6";"R_1206_3216Metric_Pad1.42x1.75mm_HandSolder";2;"5.1k";;;
67;"U2";"SOT143B";1;"PRTR5V0U2X";;;
68;"U1";"TQFP-44_10x10mm_P0.8mm";1;"ATmega32U4-AU";;;
69;"C5";"C_1206_3216Metric_Pad1.42x1.75mm_HandSolder";1;"10u";;;

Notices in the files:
projects/aaronw2_12v_boost_fan_control_12v_booster/current_version/working/working.kicad_pcb:
Copyright © 2018 by Aaron Williams
projects/aaronw2_12v_boost_fan_control_12v_booster/current_version/working/working.kicad_sch:
Copyright (C) 2018 by Aaron Williams
